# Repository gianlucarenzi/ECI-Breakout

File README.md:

# ECI-Breakout
=====================================

BreakOut Board for ECI Bus Connector Atari 130XE

This is a simple ECI Bus breakout board, useful for many purposes developing hardware for Atari 8-bit line of computers

# Rendered Images
# 
# 
# 

Hardware License
---------------------------
Copyright (C) 2018/2019 Gianluca Renzi <gianlucarenzi@eurek.it> <icjtqr@gmail.com>

The hardware of this project is released as free/open hardware under the
GNU GPL v3 License terms. See licence.txt for details.

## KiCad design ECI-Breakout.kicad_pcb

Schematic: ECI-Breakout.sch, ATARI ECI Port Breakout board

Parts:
D1: LED GREEN; LED_1206_3216Metric
ECI1: ECIBUS; ATARI-XE-ECI-SLOT
P1, P2: Conn_01x07; PinHeader_1x07_P2.54mm_Vertical
R1: 1.5K; R_1206_3216Metric_Pad1.30x1.75mm_HandSolder

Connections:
/A13: ECI1.D (A13), P1.4
/A14: ECI1.E (A14), P1.5
/A15: ECI1.F (A15), P1.6
/AUDIO: ECI1.5 (AUDIO), P2.5
/RSRVD: ECI1.A (RSRVD), P1.1
/~D1XX: ECI1.3 (~D1XX), P2.3
/~EXSEL: ECI1.1 (~EXSEL), P2.1
/~HALT: ECI1.C (~HALT), P1.3
/~IRQ: ECI1.B (~IRQ), P1.2
/~MPD: ECI1.4 (~MPD), P2.4
/~REF: ECI1.6 (~REF), P2.6
/~RST: ECI1.2 (~RST), P2.2
GND: D1.1, ECI1.H (GND), P1.7
unnamed: D1.2, R1.2
VCC: ECI1.7 (VCC), P2.7, R1.1

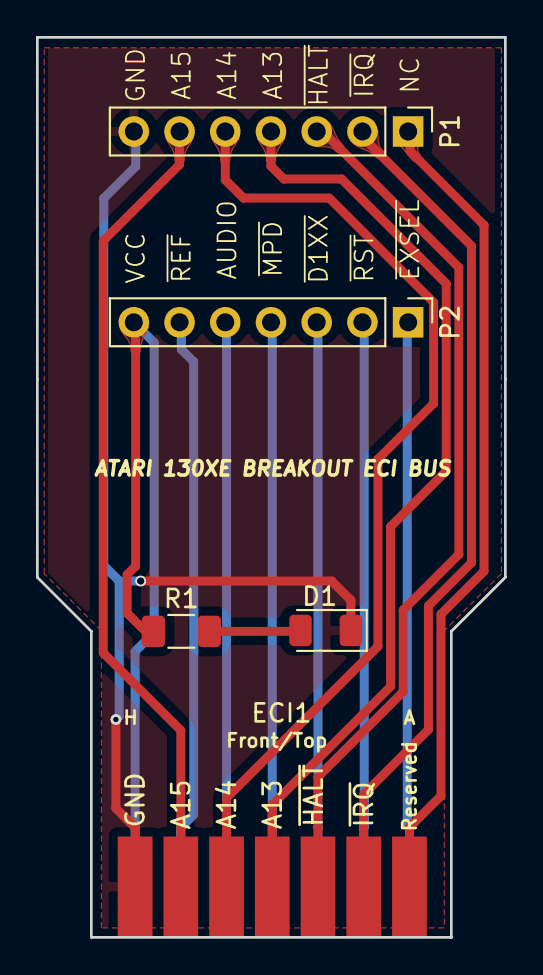
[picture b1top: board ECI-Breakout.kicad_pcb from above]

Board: 2 copper layers, 26.0 x 50.0 mm, 5 parts (0 on the bottom side), 15 nets.

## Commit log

2019-04-14 First elaborate project
2019-04-14 Added license
2019-04-14 Added images
2019-04-14 added blank spaces
2019-04-14 Modified name
2019-04-18 Added back slik names for pins
2019-06-07 Added for production to JLCPCB 2019-06-07
2025-07-24 Use PLOT from EEschema
2025-07-24 Not used
2025-07-24 UpdateUpdate to KiCAD 5.1.19
2025-07-24 Removed
2025-07-24 Added Interactive BOM
2025-07-24 Added NetList
